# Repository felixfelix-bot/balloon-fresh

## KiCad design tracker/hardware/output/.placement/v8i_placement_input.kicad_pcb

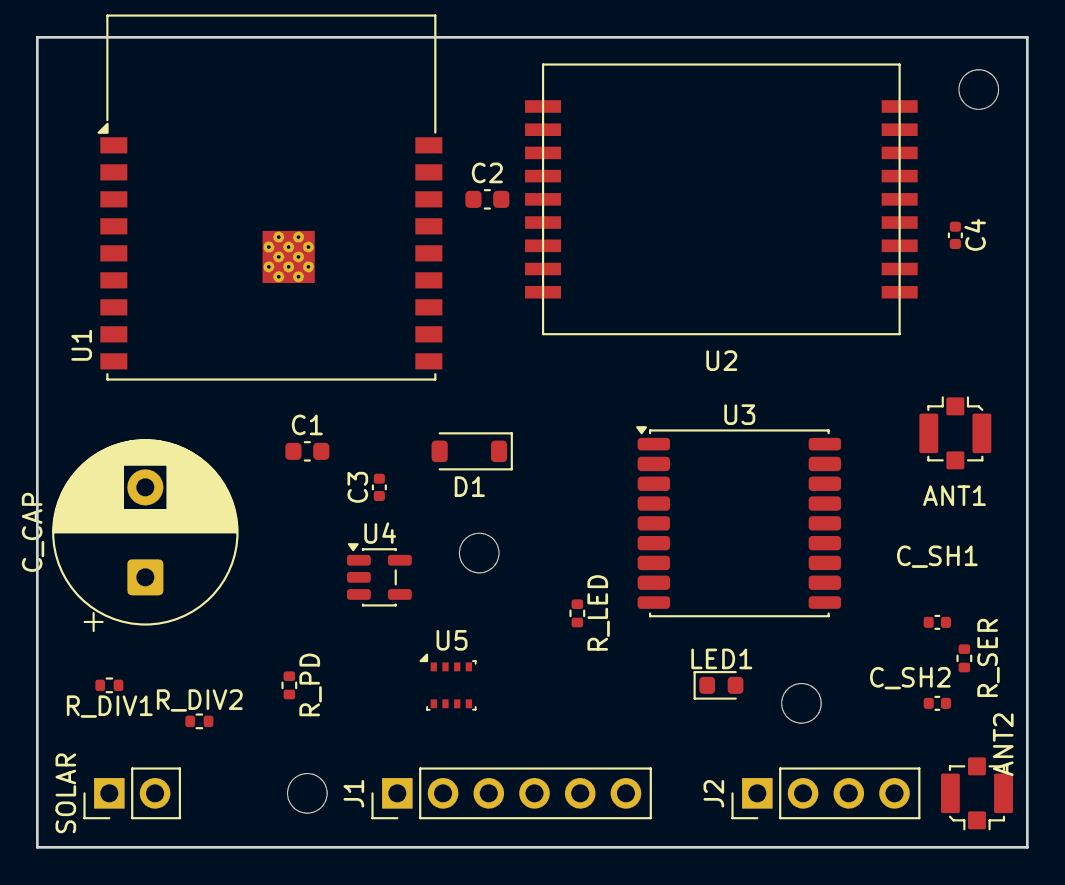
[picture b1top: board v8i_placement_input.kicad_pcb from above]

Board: 4 copper layers, 55.0 x 45.0 mm, 28 parts (0 on the bottom side), 24 nets, no tracks yet.

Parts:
ANT1: U.FL; U.FL_Molex_MCRF_73412-0110_Vertical
ANT2: U.FL_GNSS; U.FL_Molex_MCRF_73412-0110_Vertical
C1, C2: 10uF; C_0603_1608Metric
C3, C4: 100nF; C_0402_1005Metric
C_CAP: 1F_5.5V; CP_Radial_D10.0mm_P5.00mm
C_SH1, C_SH2: DNP; C_0402_1005Metric
D1: BAT54; D_SOD-123
J1: Prog_Header; PinHeader_1x06_P2.54mm_Vertical
J2: Debug_Header; PinHeader_1x04_P2.54mm_Vertical
LED1: LED_RED; LED_0603_1608Metric
MNT1, MNT2, MNT3, MNT4: MountingHole; MountingHole_2.2mm_M2
R_DIV1, R_DIV2: 100k; R_0402_1005Metric
R_LED: 330R; R_0402_1005Metric
R_PD: 10k; R_0402_1005Metric
R_SER: 0R; R_0402_1005Metric
SOLAR: Solar_In; PinHeader_1x02_P2.54mm_Vertical
U1: ESP32-C3-WROOM-02
U2: LoRa2021_Gen4; LoRa2021_Castellated
U3: MAX-M10S; ublox_MAX
U4: TPS7A02; SOT-23-5
U5: BMP280; Bosch_LGA-8_2.5x2.5mm_P0.65mm_ClockwisePinNumbering

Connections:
+3V3: C1.1, C2.1, C3.1, C4.1, J1.2, J2.2, R_PD.2, U1.1, U2.1, U3.6, U3.7, U3.8, U3.9, U4.5, U5.2, U5.6, U5.8
EN: J1.3, U1.2
GND: ANT1.2, ANT2.2, C1.2, C2.2, C3.2, C4.2, C_CAP.2, C_SH1.1, C_SH2.1, J1.1, J2.1, LED1.2, R_DIV2.2, SOLAR.2, U1.9, U1.19, U2.2, U2.8, U2.11, U2.12, U2.18, U3.1, U3.10, U3.12, U4.2, U5.1, U5.5, U5.7
GNSS_ANT: ANT2.1, C_SH2.2, R_SER.1
GNSS_RF: C_SH1.2, R_SER.2, U3.11
GPS_RX: U1.17, U3.2
GPS_TX: U1.18, U3.3
I2C_SCL: J2.4, U1.8, U5.4
I2C_SDA: J2.3, R_PD.1, U1.7, U5.3
LED_A: LED1.1, R_LED.2
LED_DRIVE: R_LED.1, U1.14
LR_BUSY: U1.3, U2.7
LR_IRQ: U1.13, U2.15
LR_RST: U1.15, U2.14
RF_OUT: ANT1.1, U2.9
SOLAR_IN: D1.1, SOLAR.1
SPI_MISO: U1.16, U2.3
SPI_MOSI: U1.6, U2.4
SPI_NSS: U1.10, U2.6
SPI_SCK: U1.5, U2.5
UART0_RX: J1.5, U1.11
UART0_TX: J1.4, U1.12
VCAP: C_CAP.1, D1.2, R_DIV1.1, U4.1, U4.3
VDIV_MID: R_DIV1.2, R_DIV2.1, U1.4

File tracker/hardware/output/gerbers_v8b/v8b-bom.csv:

Comment,Designator,Footprint,Layer,Qty
U.FL,ANT1,U.FL_Molex_MCRF_73412-0110_Vertical,top,1
10uF,C1,C_0603_1608Metric,top,1
10uF,C2,C_0603_1608Metric,top,1
100nF,C3,C_0402_1005Metric,top,1
100nF,C4,C_0402_1005Metric,top,1
1F_5.5V,C_CAP,CP_Radial_D10.0mm_P5.00mm,top,1
BAT54,D1,D_SOD-123,top,1
Prog_Header,J1,PinHeader_1x06_P2.54mm_Vertical,top,1
Debug_Header,J2,PinHeader_1x04_P2.54mm_Vertical,top,1
LED_RED,LED1,LED_0603_1608Metric,top,1
100k,R_DIV1,R_0402_1005Metric,top,1
100k,R_DIV2,R_0402_1005Metric,top,1
330R,R_LED,R_0402_1005Metric,top,1
10k,R_PD,R_0402_1005Metric,top,1
Solar_In,SOLAR,PinHeader_1x02_P2.54mm_Vertical,top,1
ESP32-C3-WROOM-02,U1,ESP32-C3-WROOM-02,top,1
LR2021F33,U2,HOPERF_RFM9XW_SMD,top,1
MAX-M10S,U3,ublox_MAX,top,1
TPS7A02,U4,SOT-23-5,top,1
MS5611,U5,Package_LGA:LGA-8_3x5mm_P1.25mm,top,1

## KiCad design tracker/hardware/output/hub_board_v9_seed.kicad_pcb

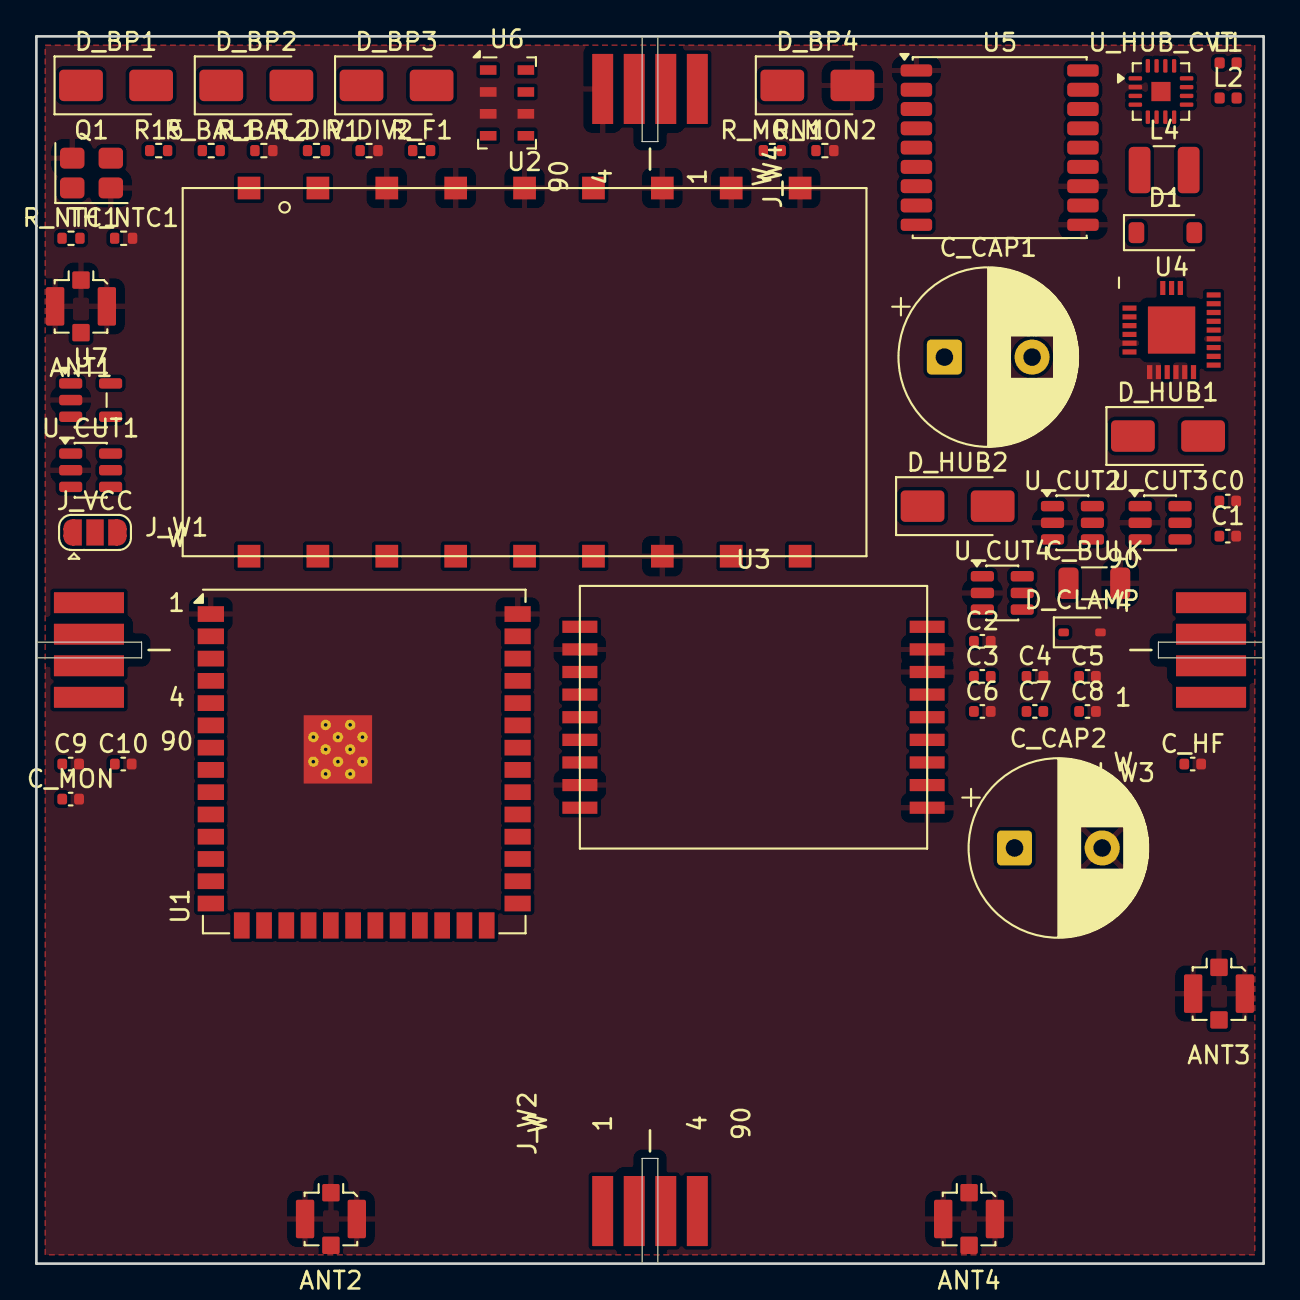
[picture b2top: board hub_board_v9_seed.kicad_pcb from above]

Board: 4 copper layers, 70.0 x 70.0 mm, 59 parts (0 on the bottom side), 59 nets, no tracks yet.

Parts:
ANT1: U.FL_433_TX; U.FL_Molex_MCRF_73412-0110_Vertical
ANT2: U.FL_2G4_RANGE; U.FL_Molex_MCRF_73412-0110_Vertical
ANT3: U.FL_2G4_RX; U.FL_Molex_MCRF_73412-0110_Vertical
ANT4: U.FL_GNSS_L1; U.FL_Molex_MCRF_73412-0110_Vertical
C0: 0.8pF; C_0402_1005Metric
C1, C2: 1.2pF; C_0402_1005Metric
C3: 100pF; C_0402_1005Metric
C4: 10uF; C_0402_1005Metric
C5, C6: 10nF; C_0402_1005Metric
C7: 0.5pF; C_0402_1005Metric
C8, C10: 100nF; C_0402_1005Metric
C9: 470nF; C_0402_1005Metric
C_BULK: 100uF; C_1206_3216Metric
C_CAP1, C_CAP2: 3.3F 2.7V (AVX SCC); CP_Radial_D10.0mm_P5.00mm
C_HF: 100nF; C_0402_1005Metric
C_MON: 10nF; C_0402_1005Metric
D1: BAT54; D_SOD-123
D_BP1, D_BP2, D_BP3, D_BP4: SS24; D_SMA
D_CLAMP: TVS clamp (set point TODO(unverified)); D_SOD-323
D_HUB1, D_HUB2: SS24; D_SMA
J_VCC: F33_VCC_SEL (5V raw | 3V3); SolderJumper-3_P1.3mm_Open_RoundedPad1.0x1.5mm
J_W1: WING_SOCKET_4P (hub wing interface 1); Wing_Tab_4P
J_W2: WING_SOCKET_4P (hub wing interface 2); Wing_Tab_4P
J_W3: WING_SOCKET_4P (hub wing interface 3); Wing_Tab_4P
J_W4: WING_SOCKET_4P (hub wing interface 4); Wing_Tab_4P
L1: 3.0nH; L_0402_1005Metric
L2: 2.5nH; L_0402_1005Metric
L4: 15uH; L_1210_3225Metric
Q1: 52MHz; Crystal_SMD_3225-4Pin_3.2x2.5mm
R15: 0R; R_0402_1005Metric
R_BAL1, R_BAL2: 10k; R_0402_1005Metric
R_DIV1, R_DIV2: 1M; R_0402_1005Metric
R_F1: 100R; R_0402_1005Metric
R_MON1, R_MON2: 4.7M; R_0402_1005Metric
R_NTC1: TODO(unverified) (sets ntc_r_ratio); R_0402_1005Metric
TH_NTC1: TODO(unverified) (NTC, R25/beta TODO); R_0402_1005Metric
U1: ESP32-S3-WROOM-1U-N8R8; ESP32-S3-WROOM-1U
U2: LoRa2021F33-2G4; LoRa2021F33_2G4
U3: LoRa2021_Castellated
U4: SX1280; SX1280_QFN24
U5: MAX-M10S; ublox_MAX
U6: MS5611-01BA; LGA-8_3x5mm_P1.25mm
U7: TPS7A02; SOT-23-5
U_CUT1, U_CUT2, U_CUT3, U_CUT4: SN74LVC1G373DBVR; SOT-23-6
U_HUB_CVT: BQ25504RGTR; VQFN-16-1EP_3x3mm_P0.5mm_EP1.1x1.1mm

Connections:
+3V3: C10.1, J_VCC.3, R15.1, R_F1.1, U1.2, U2.5, U3.1, U4.15, U5.6, U5.7, U5.9, U6.1, U6.4, U6.5, U7.5
/ANT1_433_TX: ANT1.1, U2.9
/ANT2_2G4_RANGE: ANT2.1, C3.2
/ANT3_2G4_RX: ANT3.1, U3.10
/ANT4_GNSS_L1: ANT4.1, U5.11
/CUT_SENSE_W1: J_W1.3, U_CUT1.3
/CUT_SENSE_W2: J_W2.3, U_CUT2.3
/CUT_SENSE_W3: J_W3.3, U_CUT3.3
/CUT_SENSE_W4: J_W4.3, U_CUT4.3
/F33_BUSY: U1.12, U2.14
/F33_CS_N: U1.7, U2.13
/F33_IRQ: U1.17, U2.18
/F33_MISO: U1.6, U2.16, U3.3
/F33_MOSI: U1.5, U2.15, U3.4
/F33_RESET_N: U1.18, U2.17
/F33_SCK: U1.4, U2.12, U3.5
/F33_VCC: C_BULK.1, C_HF.1, D_CLAMP.1, J_VCC.2, R_MON1.1, U2.1
/F33_VSENSE: C_MON.1, R_MON1.2, R_MON2.1, U1.21
/GNSS_PPS: U1.23, U5.4
/GNSS_RX: U1.37, U5.3
/GNSS_TX: U1.36, U5.2
/GNSS_VCC: C4.1, R_F1.2, U5.8
/HUB_PV_MID1: D_HUB1.2, D_HUB2.1
/HUB_PV_N: D_HUB2.2, U_HUB_CVT.3
/HUB_PV_P: D_HUB1.1, U_HUB_CVT.1
/I2C_SCL: U1.38, U6.8
/I2C_SDA: U1.39, U6.7
/NTC_SENSE: R_NTC1.2, TH_NTC1.1
/SCAP_ADC: R_DIV1.2, R_DIV2.1
/SCAP_MID: C_CAP1.2, C_CAP2.1, R_BAL1.2, R_BAL2.1
/SX1280_BUSY: U1.31, U4.7
/SX1280_CS_N: U1.10, U4.19
/SX1280_DCC_SW: L4.1, U4.14
/SX1280_DIO1: U1.33, U4.8
/SX1280_DIO2: U1.11, U4.9
/SX1280_DIO3: U1.34, U4.10
/SX1280_MISO: U1.9, U4.16
/SX1280_MOSI: U1.8, U4.17
/SX1280_RESET_N: U1.32, U4.3
/SX1280_RF: C0.1, L1.1, U4.22
/SX1280_RF_FILT: C2.1, C3.1, C7.2, L2.2
/SX1280_RF_MATCH: C1.1, C7.1, L1.2, L2.1
/SX1280_SCK: U1.22, U4.18
/SX1280_VBAT_IO: C8.1, R15.2, U4.11
/SX1280_VDD: C6.1, C9.1, L4.2, U4.2, U4.12
/SX1280_VR_PA: C5.1, U4.1
/SX1280_XTA: Q1.1, U4.4
/SX1280_XTB: Q1.3, U4.6
/U3_BUSY: U1.24, U3.7
/U3_CS_N: U1.20, U3.6
/U3_IRQ: U1.19, U3.15
/U3_RESET_N: U1.25, U3.14
/VSCAP: C_CAP1.1, D1.1, J_VCC.1, R_BAL1.1, R_DIV1.1, U7.1, U7.3, U_CUT1.1, U_CUT2.1, U_CUT3.1, U_CUT4.1
/VTCXO_VNTC: R_NTC1.1, U3.13
/W1_SOLAR_N: D_BP1.2, D_BP2.1, J_W1.4, J_W2.1
/W1_SOLAR_P: D1.2, D_BP1.1, J_W1.1
/W2_SOLAR_N: D_BP2.2, D_BP3.1, J_W2.4, J_W3.1
/W3_SOLAR_N: D_BP3.2, D_BP4.1, J_W3.4, J_W4.1
GND: ANT1.2, ANT2.2, ANT3.2, ANT4.2, C0.2, C1.2, C2.2, C4.2, C5.2, C6.2, C8.2, C9.2, C10.2, C_BULK.2, C_CAP2.2, C_HF.2, C_MON.2, D_BP4.2, D_CLAMP.2, J_W1.2, J_W2.2, J_W3.2, J_W4.2, J_W4.4, Q1.2, Q1.4, R_BAL2.2, R_DIV2.2, R_MON2.2, TH_NTC1.2, U1.1, U1.40, U1.41, U2.2, U2.3, U2.4, U2.6, U2.7, U2.8, U2.11, U3.2, U3.8, U3.11, U3.12, U3.18, U4.0, U4.5, U4.13, U4.20, U4.21, U4.23, U4.24, U5.1, U5.10, U5.12, U6.2, U6.3, U6.6, U7.2, U_CUT1.2, U_CUT2.2, U_CUT3.2, U_CUT4.2, U_HUB_CVT.2

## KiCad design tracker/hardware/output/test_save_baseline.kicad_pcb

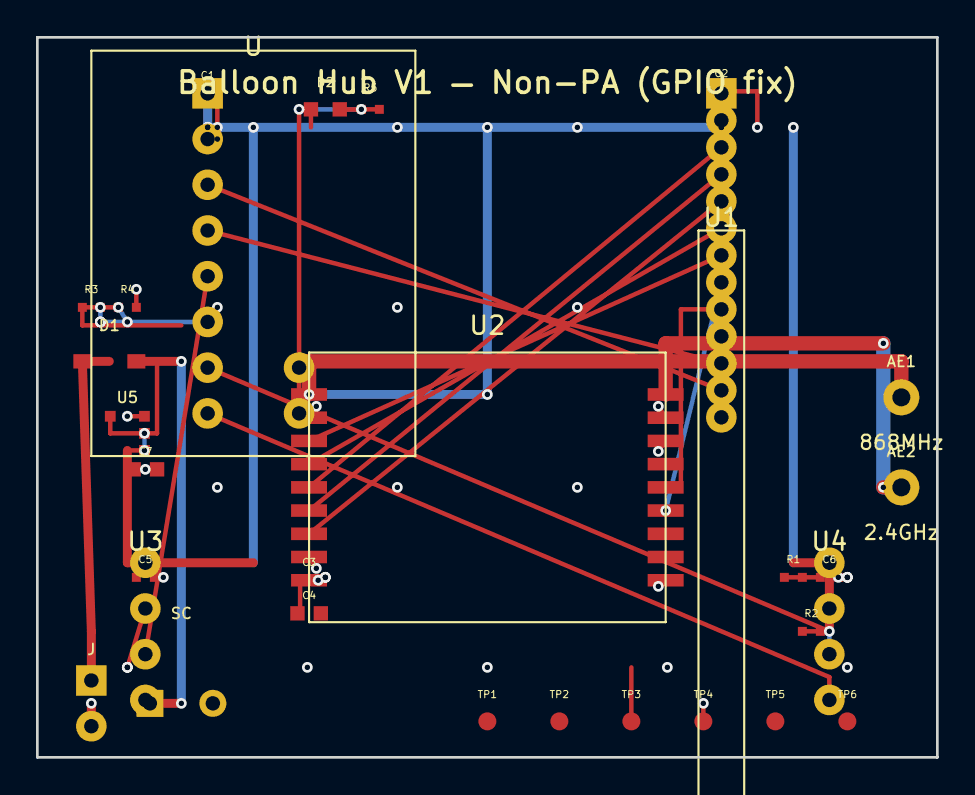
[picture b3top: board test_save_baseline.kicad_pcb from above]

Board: 2 copper layers, 50.0 x 40.0 mm, 30 parts (0 on the bottom side), 21 nets.

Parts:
AE1: 868MHz; TestPoint_THTPad_D2.0mm_Drill1.0mm
AE2: 2.4GHz; TestPoint_THTPad_D2.0mm_Drill1.0mm
C1, C2, C3, C5, C6: 100nF; C_0402_1005Metric
C4, C7: 10uF; C_0805_2012Metric
D1: BAT54; D_SOD-123
D2: STATUS; LED_0603_1608Metric
J: SOLAR; PinHeader_1x02_P2.54mm_Vertical
R1, R2: 4.7k; R_0402_1005Metric
R3, R4: 1M; R_0402_1005Metric
R5: 330R; R_0402_1005Metric
SC: 1F 5.5V; CP_Radial_D8.0mm_P3.50mm
TP1: SPI0_SCK; TestPoint_Pad_D1.0mm
TP2: SPI0_MOSI; TestPoint_Pad_D1.0mm
TP3: 3V3; TestPoint_Pad_D1.0mm
TP4: GND; TestPoint_Pad_D1.0mm
TP5: LED_GPIO18; TestPoint_Pad_D1.0mm
TP6: FEM_TX_GPIO19; TestPoint_Pad_D1.0mm
U: ESP32-C3-Mini-1; ESP32-C3_Mini_V1_Header
U1: RP2040-Zero; PinHeader_1x13_P2.54mm_Vertical
U2: LoRa2021; LoRa2021_Castellated
U3: MAX-M10S; PinHeader_1x04_P2.54mm_Vertical
U4: MS5611; PinHeader_1x04_P2.54mm_Vertical
U5: TPS7A02; SOT-23-5

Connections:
3V3: C1.1, C2.1, C3.1, C4.1, C5.1, C6.1, C7.1, R1.1, R2.1, TP3.1, U.1, U1.1, U2.1, U3.1, U4.1, U5.5
ESP_TX_RP2040_RX: U.3, U1.12
GND: C1.2, C2.2, C3.2, C4.2, C5.2, C6.2, C7.2, D2.1, J.2, R4.2, SC.2, TP4.1, U.2, U1.2, U1.13, U2.2, U2.8, U2.11, U2.12, U2.18, U3.2, U4.2, U5.2
GPS_TX_ESP_RX: U.5, U3.3
I2C_SCL: R2.2, U.8, U4.4
I2C_SDA: R1.2, U.7, U4.3
LED_ANODE: D2.2, R5.2
LR2021_BUSY: U1.7, U2.7
LR2021_DIO9: U1.8, U2.15
LR2021_RST: U1.9, U2.14
RF_2G4_2400: AE2.1, U2.10
RF_SUB_868: AE1.1, U2.9
RP2040_TX_ESP_RX: U.4, U1.11
SOLAR_IN: D1.1, J.1
SPI0_MISO: U1.5, U2.3
SPI0_MOSI: TP2.1, U1.4, U2.4
SPI0_NSS: U1.6, U2.6
SPI0_SCK: TP1.1, U1.3, U2.5
STATUS_LED: R5.1, TP5.1
VCAP: D1.2, R3.1, SC.1, U5.1, U5.3
VDIV_MID: R3.2, R4.1, U.6

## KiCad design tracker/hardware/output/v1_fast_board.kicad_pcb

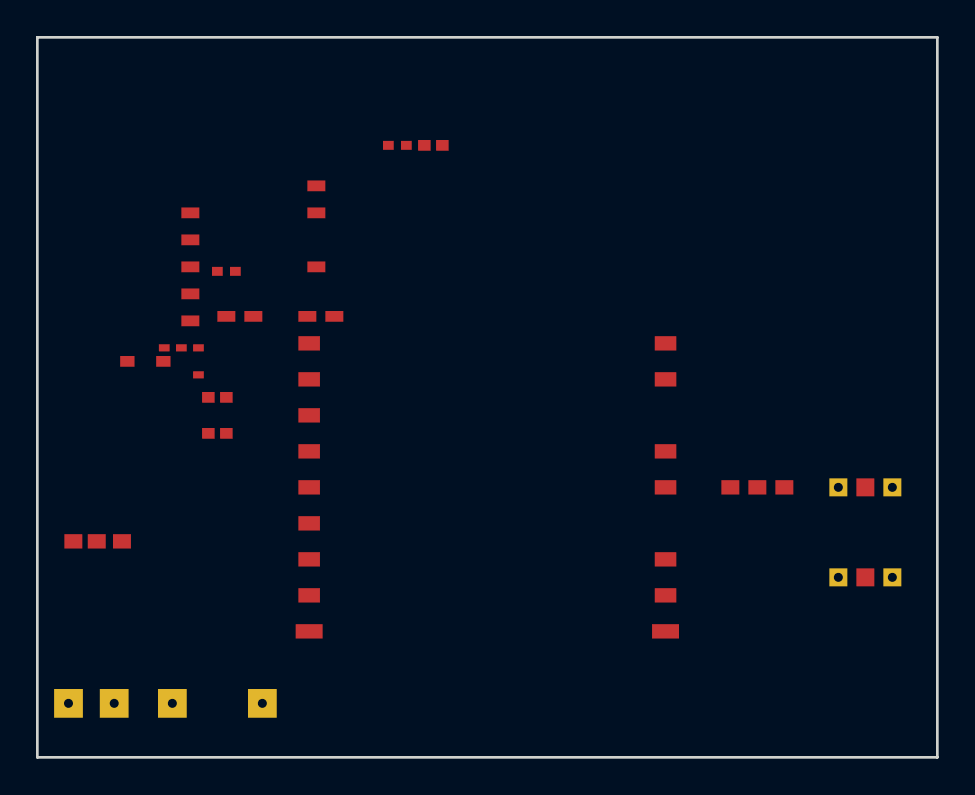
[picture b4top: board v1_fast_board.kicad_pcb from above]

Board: 2 copper layers, 50.0 x 40.0 mm, 15 parts (0 on the bottom side), 17 nets, no tracks yet.

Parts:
ANT1: U.FL-868
ANT2: U.FL-2400
C1, C2: 10uF
C_CAP: Supercap
D1: BAT54
FEM: FEM
LED1: LED-0603
R_LED: 330R
R_PD: 10k
SOLAR: Solar-Conn
U1: ESP32-C3
U2: LR2021F33
U3: MAX-M10S
U4: TPS7A02

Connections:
3V3: C2.1, FEM.VCC, U1.VCC, U2.1, U3.1, U4.4
FEM_TX: FEM.TX, U1.GPIO19
GND: ANT1.2, ANT1.3, ANT2.2, ANT2.3, C1.2, C2.2, C_CAP.2, FEM.GND, LED1.K, R_PD.1, SOLAR.2, U1.GND, U2.2, U2.8, U2.10, U2.11, U2.16, U2.17, U3.2, U4.2
GPS_RX: U1.GPIO1, U3.3
LED_ANODE: LED1.A, R_LED.2
LR2021_BUSY: U1.GPIO4, U2.7
LR2021_DIO9: U1.GPIO5, U2.13
LR2021_RST: U1.GPIO3, U2.14
RF_2G4_2400: ANT2.1, U2.18
RF_SUB_868: ANT1.1, U2.9
SOLAR_IN: D1.A, SOLAR.1
SPI_MISO: R_PD.2, U1.GPIO2, U2.3
SPI_MOSI: U1.GPIO7, U2.4
SPI_NSS: U1.GPIO10, U2.6
SPI_SCK: U1.GPIO6, U2.5
STATUS_LED: R_LED.1, U1.GPIO9
VCAP: C1.1, C_CAP.1, D1.K, U4.1, U4.3
